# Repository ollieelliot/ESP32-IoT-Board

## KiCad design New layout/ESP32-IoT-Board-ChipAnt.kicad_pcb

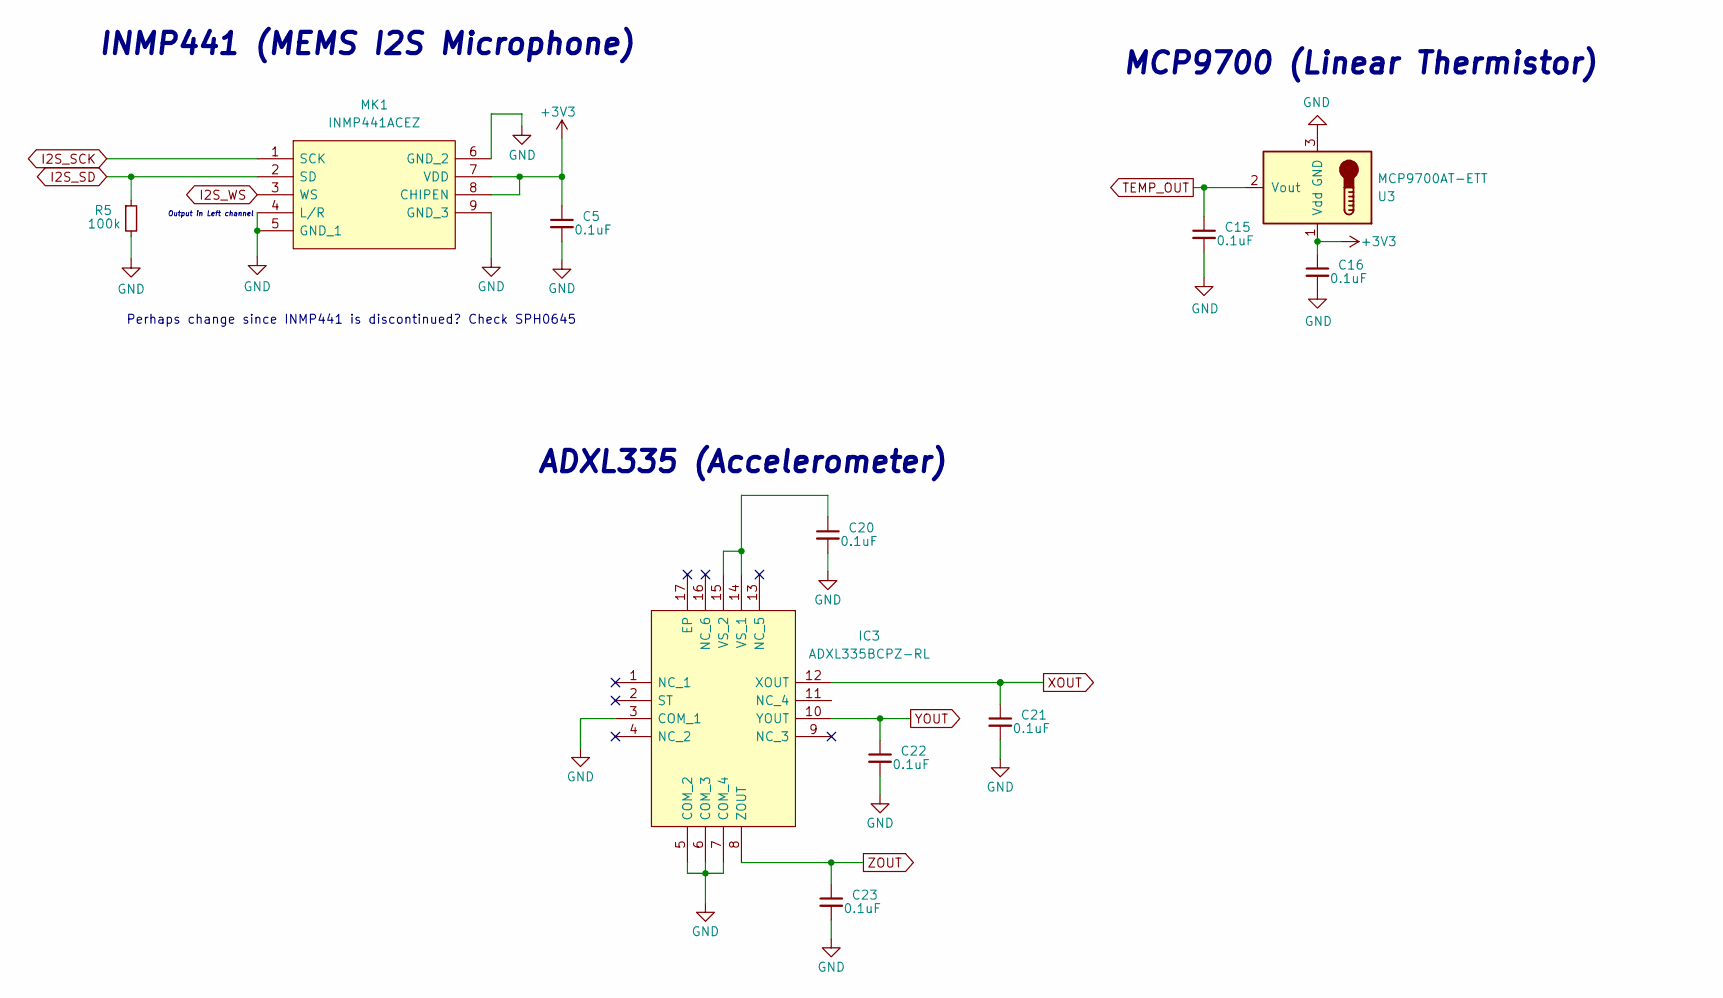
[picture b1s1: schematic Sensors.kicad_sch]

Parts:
C5, C15, C16, C20, C21, C22, C23: 0.1uF; C_0402_1005Metric
IC3: ADXL335BCPZ-RL; LFCSP-16-1EP_4x4mm_P0.65mm_EP2.1x2.1mm; Manufacturer_Part_Number ADXL335BCPZ-RL; Mouser Part Number 584-ADXL335BCPZ-R
MK1: INMP441ACEZ; Manufacturer_Part_Number INMP441ACEZ
R5: 100k; R_0402_1005Metric
U3: MCP9700AT-ETT; SOT-23

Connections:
+3V3: C5.1, C16.1, MK1.7 (VDD), MK1.8 (CHIPEN), U3.1 (Vdd); also elsewhere on the board
GND: C5.2, C15.2, C16.2, C20.2, C21.2, C22.2, C23.2, IC3.3 (COM_1), IC3.5 (COM_2), IC3.6 (COM_3), IC3.7 (COM_4), MK1.4 (L/R), MK1.5 (GND_1), MK1.6 (GND_2), MK1.9 (GND_3), R5.2, U3.3 (GND); also elsewhere on the board
I2S_SCK: MK1.1 (SCK); also elsewhere on the board
I2S_SD: MK1.2 (SD), R5.1; also elsewhere on the board
I2S_WS: MK1.3 (WS); also elsewhere on the board
unnamed: C20.1, IC3.14 (VS_1), IC3.15 (VS_2)
TEMP_OUT: C15.1, U3.2 (Vout); also elsewhere on the board
XOUT: C21.1, IC3.12 (XOUT); also elsewhere on the board
YOUT: C22.1, IC3.10 (YOUT); also elsewhere on the board
ZOUT: C23.1, IC3.8 (ZOUT); also elsewhere on the board

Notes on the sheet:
MCP9700 (Linear Thermistor)
ADXL335 (Accelerometer)
INMP441 (MEMS I2S Microphone)
Output in Left channel
Perhaps change since INMP441 is discontinued? Check SPH0645

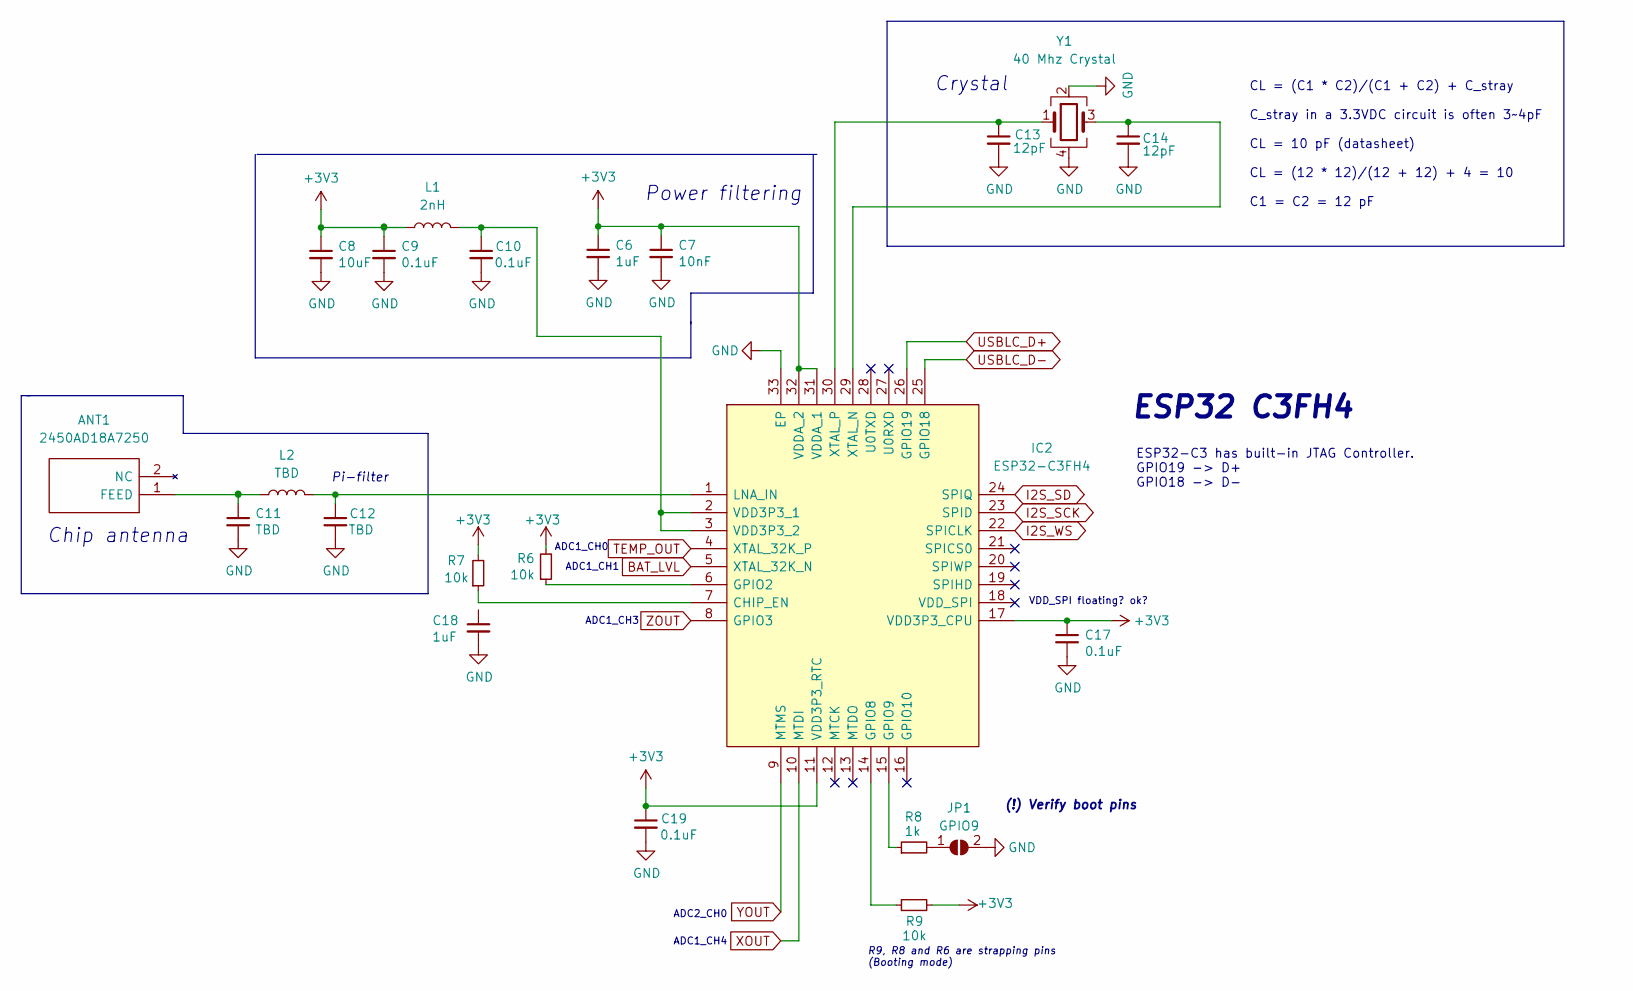
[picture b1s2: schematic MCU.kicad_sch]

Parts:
ANT1: 2450AD18A7250; ANTC3216X60N; Manufacturer_Part_Number 2450AD18A7250; Mouser Part Number 609-2450AD18A7250
C6, C18: 1uF; C_0402_1005Metric
C7: 10nF; C_0402_1005Metric
C8: 10uF; C_0402_1005Metric
C9, C10, C17, C19: 0.1uF; C_0402_1005Metric
C11, C12: TBD; C_0402_1005Metric
C13, C14: 12pF; C_0402_1005Metric
IC2: ESP32-C3FH4; QFN50P500X500X90-33N-D; Manufacturer_Part_Number ESP32-C3FH4; Mouser Part Number 356-ESP32-C3FH4
JP1: GPIO9; R_0402_1005Metric
L1: 2nH; L_0603_1608Metric
L2: TBD; L_0402_1005Metric
R6, R7, R9: 10k; R_0402_1005Metric
R8: 1k; R_0402_1005Metric
Y1: 40 Mhz Crystal; ECS4001037B2CKMTR

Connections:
+3V3: C6.1, C7.1, C8.1, C9.1, C17.1, C19.1, IC2.11 (VDD3P3_RTC), IC2.17 (VDD3P3_CPU), IC2.31 (VDDA_1), IC2.32 (VDDA_2), L1.1, R6.2, R7.2, R9.2; also elsewhere on the board
BAT_LVL: IC2.5 (XTAL_32K_N); also elsewhere on the board
GND: C6.2, C7.2, C8.2, C9.2, C10.2, C11.2, C12.2, C13.2, C14.2, C17.2, C18.2, C19.2, IC2.33 (EP), JP1.2 (B), Y1.2, Y1.4; also elsewhere on the board
I2S_SCK: IC2.23 (SPID); also elsewhere on the board
I2S_SD: IC2.24 (SPIQ); also elsewhere on the board
I2S_WS: IC2.22 (SPICLK); also elsewhere on the board
unnamed: ANT1.1 (FEED), C11.1, L2.1
unnamed: C10.1, IC2.2 (VDD3P3_1), IC2.3 (VDD3P3_2), L1.2
unnamed: C12.1, IC2.1 (LNA_IN), L2.2
unnamed: C13.1, IC2.30 (XTAL_P), Y1.1
unnamed: C14.1, IC2.29 (XTAL_N), Y1.3
unnamed: IC2.6 (GPIO2), R6.1
unnamed: IC2.7 (CHIP_EN), R7.1
unnamed: IC2.14 (GPIO8), R9.1
unnamed: IC2.15 (GPIO9), R8.1
unnamed: JP1.1 (A), R8.2
TEMP_OUT: IC2.4 (XTAL_32K_P); also elsewhere on the board
USBLC_D+: IC2.26 (GPIO19); also elsewhere on the board
USBLC_D-: IC2.25 (GPIO18); also elsewhere on the board
XOUT: IC2.10 (MTDI); also elsewhere on the board
YOUT: IC2.9 (MTMS); also elsewhere on the board
ZOUT: IC2.8 (GPIO3); also elsewhere on the board

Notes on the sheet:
CL = (C1 * C2)/(C1 + C2) + C_stray C_stray in a 3.3VDC circuit is often 3~4pF CL = 10 pF (datasheet) CL = (12 * 12)/(12 + 12) + 4 = 10 C1 = C2 = 12 pF
ESP32-C3 has built-in JTAG Controller. GPIO19 -> D+ GPIO18 -> D-
ADC2_CH0
Crystal
(!) Verify boot pins
ADC1_CH4
ADC1_CH1
ESP32 C3FH4
Pi-filter
Power filtering
Chip antenna
VDD_SPI floating? ok?
ADC1_CH0
R9, R8 and R6 are strapping pins (Booting mode)
ADC1_CH3

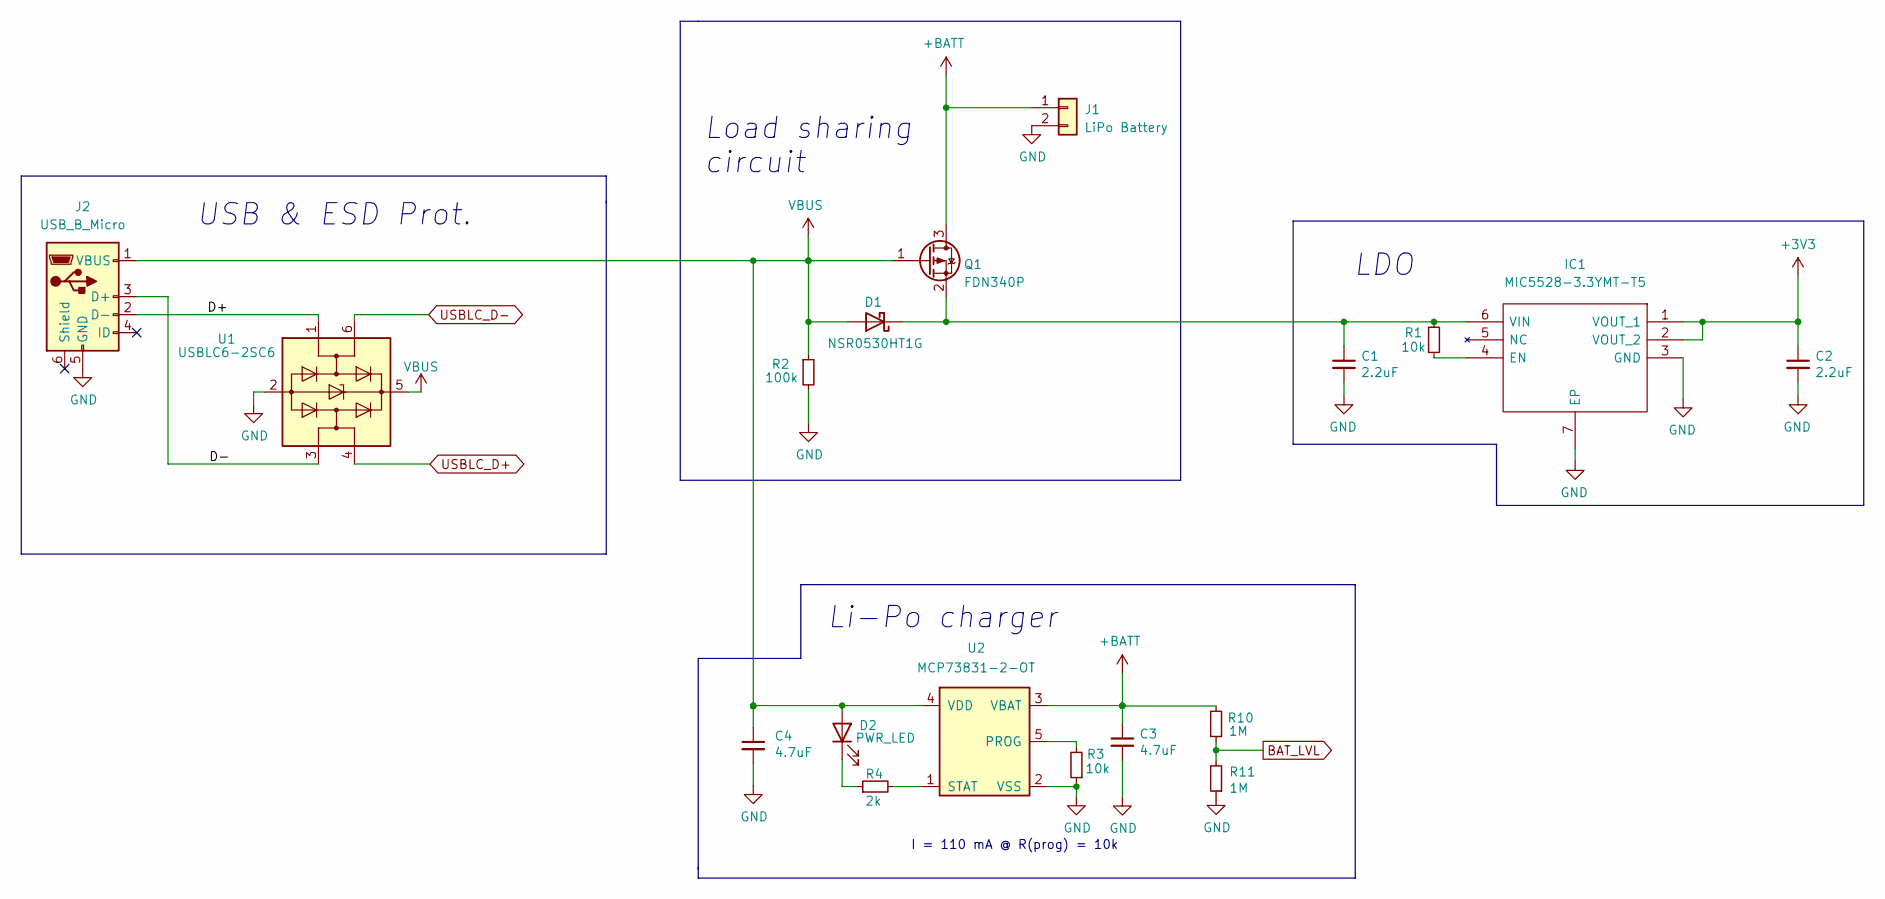
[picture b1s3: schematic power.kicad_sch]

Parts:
C1, C2: 2.2uF; C_0402_1005Metric
C3, C4: 4.7uF; C_0402_1005Metric
D1: NSR0530HT1G; D_SOD-323
D2: PWR_LED; LED_0603_1608Metric
IC1: MIC5528-3.3YMT-T5; TDFN-6-1EP_2.5x2.5mm_P0.65mm_EP1.3x2mm; Manufacturer_Part_Number MIC5528-3.3YMT-T5; Mouser Part Number 998-MIC5528-3.3YMTT5
J1: LiPo Battery; JST_PH_S2B-PH-K_1x02_P2.00mm_Horizontal
J2: USB_B_Micro; USB_Micro-B_Molex_47346-0001
Q1: FDN340P; SOT-23
R1, R3: 10k; R_0402_1005Metric
R2: 100k; R_0402_1005Metric
R4: 2k; R_0402_1005Metric
R10, R11: 1M; R_0402_1005Metric
U1: USBLC6-2SC6; SOT-23-6
U2: MCP73831-2-OT; SOT-23-5

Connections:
+3V3: C2.1, IC1.1 (VOUT_1), IC1.2 (VOUT_2); also elsewhere on the board
+BATT: C3.1, J1.1, Q1.3 (D), R10.2, U2.3 (VBAT)
/USB & Power/D+: J2.2 (D-), U1.1 (I/O1)
/USB & Power/D-: J2.3 (D+), U1.3 (I/O2)
BAT_LVL: R10.1, R11.2; also elsewhere on the board
GND: C1.2, C2.2, C3.2, C4.2, IC1.3 (GND), IC1.7 (EP), J1.2, J2.5 (GND), R2.2, R3.1, R11.1, U1.2 (GND), U2.2 (VSS); also elsewhere on the board
unnamed: C1.1, D1.1 (K), IC1.6 (VIN), Q1.2 (S), R1.1
unnamed: D2.1 (K), R4.1
unnamed: IC1.4 (EN), R1.2
unnamed: R3.2, U2.5 (PROG)
unnamed: R4.2, U2.1 (STAT)
USBLC_D+: U1.4 (I/O2); also elsewhere on the board
USBLC_D-: U1.6 (I/O1); also elsewhere on the board
VBUS: C4.1, D1.2 (A), D2.2 (A), J2.1 (VBUS), Q1.1 (G), R2.1, U1.5 (VBUS), U2.4 (VDD)

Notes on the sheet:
Li-Po charger
I = 110 mA @ R(prog) = 10k
USB & ESD Prot.
LDO
Load sharing circuit

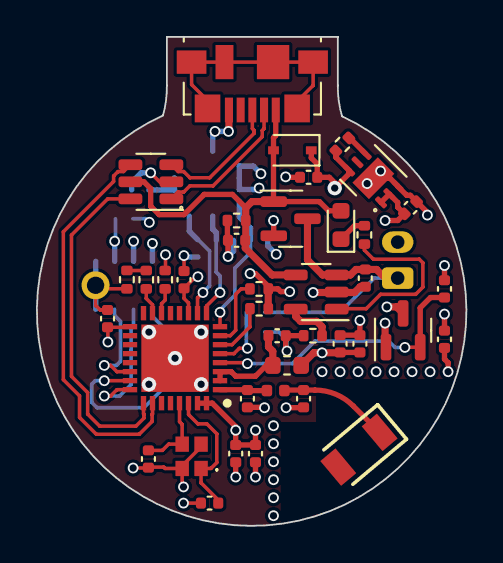
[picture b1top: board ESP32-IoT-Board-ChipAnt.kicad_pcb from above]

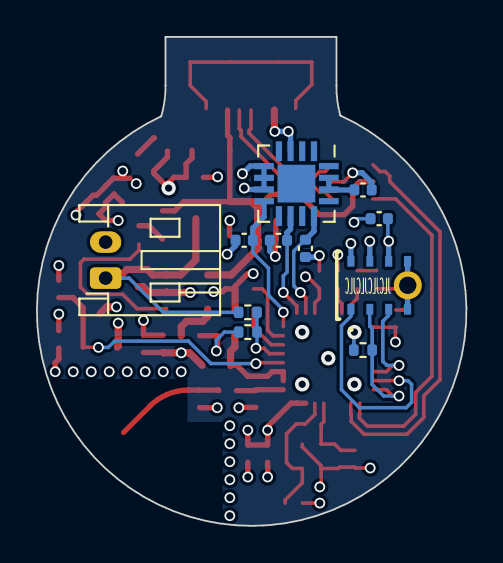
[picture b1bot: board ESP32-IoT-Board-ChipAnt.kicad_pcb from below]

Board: 4 copper layers, 23.9 x 27.2 mm, 50 parts (11 on the bottom side), 32 nets.

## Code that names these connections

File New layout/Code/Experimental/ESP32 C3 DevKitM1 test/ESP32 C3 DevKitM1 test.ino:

#include <driver/i2s.h>

#define I2S_SD 4
#define I2S_SCK 6
#define I2S_WS 5

#define I2S_PORT I2S_NUM_0


#define bufferLen 64
int16_t sBuffer[bufferLen];
 
void i2s_install() {
  // Set up I2S Processor configuration
  const i2s_config_t i2s_config = {
    .mode = i2s_mode_t(I2S_MODE_MASTER | I2S_MODE_RX),
    .sample_rate = 44100,
    .bits_per_sample = i2s_bits_per_sample_t(16),
    .channel_format = I2S_CHANNEL_FMT_ONLY_LEFT,
    .communication_format = i2s_comm_format_t(I2S_COMM_FORMAT_STAND_I2S),
    .intr_alloc_flags = 0,
    .dma_buf_count = 8,
    .dma_buf_len = bufferLen,
    .use_apll = false
  };
 
  i2s_driver_install(I2S_PORT, &i2s_config, 0, NULL);
}
 
void i2s_setpin() {
  // Set I2S pin configuration
  const i2s_pin_config_t pin_config = {
    .bck_io_num = I2S_SCK,
    .ws_io_num = I2S_WS,
    .data_out_num = -1,
    .data_in_num = I2S_SD
  };
 
  i2s_set_pin(I2S_PORT, &pin_config);
}
 
void setup() {
 
  // Set up Serial Monitor
  Serial.begin(115200);
  Serial.println(" ");
 
  delay(1000);
 
  // Set up I2S
  i2s_install();
  i2s_setpin();
  i2s_start(I2S_PORT);
 
 
  delay(500);
}
 
void loop() {
 
  // False print statements to "lock range" on serial plotter display
  // Change rangelimit value to adjust "sensitivity"
  /*
  int rangelimit = 3000;
  Serial.print(rangelimit * -1);
  Serial.print(" ");
  Serial.print(rangelimit);
  Serial.print(" ");
  */
  // Get I2S data and place in data buffer
  size_t bytesIn = 0;
  esp_err_t result = i2s_read(I2S_PORT, &sBuffer, bufferLen, &bytesIn, portMAX_DELAY);
 
  if (result == ESP_OK)
  {
    // Read I2S data buffer
    int16_t samples_read = bytesIn / 8;
    if (samples_read > 0) {
      float mean = 0;
      for (int16_t i = 0; i < samples_read; ++i) {
        mean += (sBuffer[i]);
      }
 
      // Average the data reading
      mean /= samples_read;
 
      // Print to serial plotter
      Serial.println(mean);
    }
  }
}

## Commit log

2022-02-27 Added IMP441 MEMS Microphone
2022-03-12 Added thermistor and continued to add necessary components
2022-03-16 Initial commit of new circuit
2022-03-31 First draft of PCB
2022-12-12 Changed almost everything
2022-12-14 Added accelerometer
2022-12-17 Added experimental code
2022-12-20 Made new layout
2022-12-20 New layout
2023-01-26 Final
